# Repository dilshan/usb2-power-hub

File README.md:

4 Port high power USB hub 
=========================

This project is about a high current USB 2.0 hub that is specifically designed to drive USB powered development boards and experimental peripherals.

The core element of this USB hub is the *FE1.1s* USB 2.0 hub controller. The *FE1.1s* is a low cost, 4-port, high-speed USB hub controller you should be able to find on *eBay* or AliExpress.

This USB hub adds the following additional features to those offered by the *FE1.1s*:

 - Switches to on/off and reset individual USB ports.
 - Capability to provide a maximum of 3A of current from each USB port.
 - Power using 9V to 15V DC voltage source.

This USB hub uses a *PIC16F630* MCU and four *LM2596-5.0* switching regulators. 

[You can find everything about how to build and use this project on our wiki.](https://github.com/dilshan/usb2-power-hub/wiki)

Licenses
--------

This is a [certified open hardware project](https://certification.oshwa.org/lk000005.html) and all its design files, firmware source code, documentation, and other resource files are available at this project source repository. The content of this project is distributed under the terms of the following licenses:

 - Hardware License: [CC BY 4.0](https://creativecommons.org/licenses/by/4.0/)
 - Software License: [MIT](https://github.com/dilshan/usb-morse-keyer/blob/master/LICENSE)
 - Documentation License: [CC BY 4.0](https://creativecommons.org/licenses/by/4.0/)

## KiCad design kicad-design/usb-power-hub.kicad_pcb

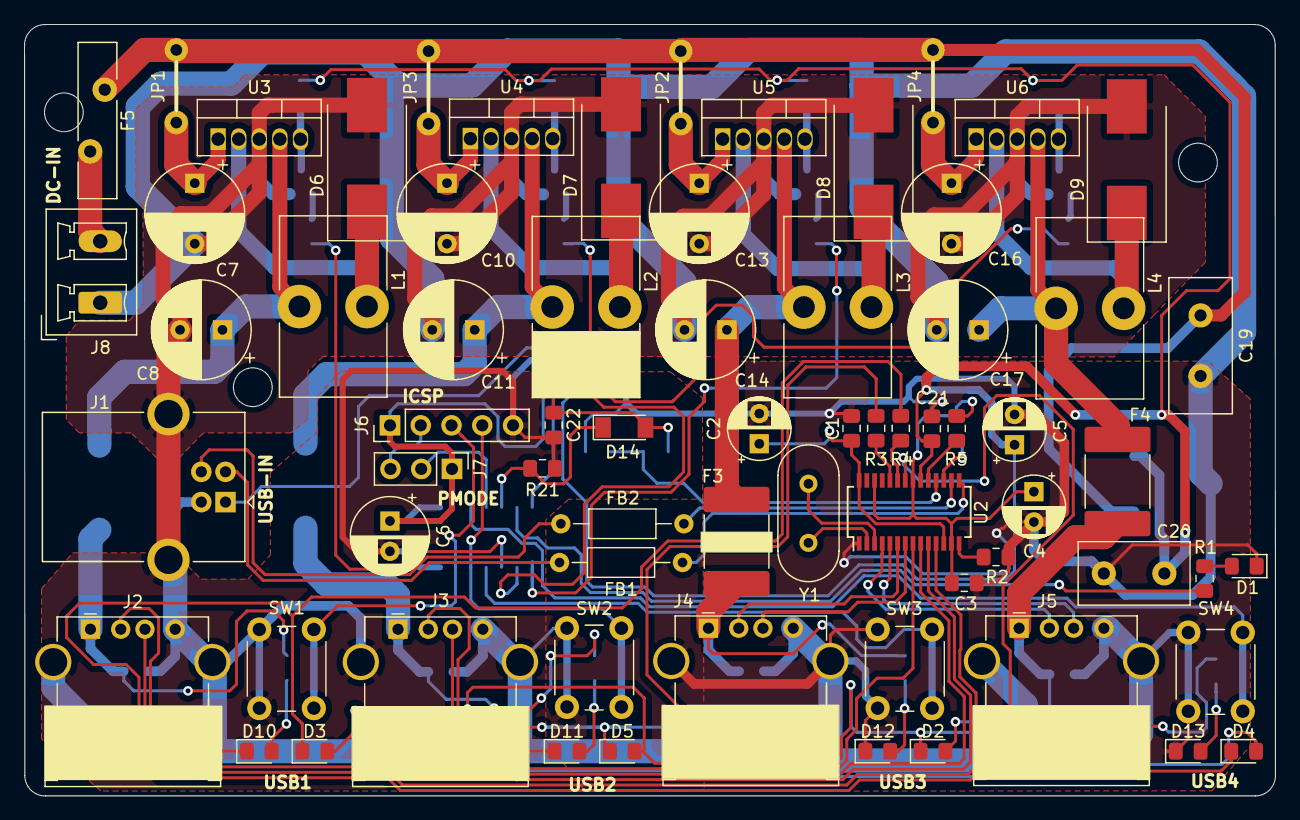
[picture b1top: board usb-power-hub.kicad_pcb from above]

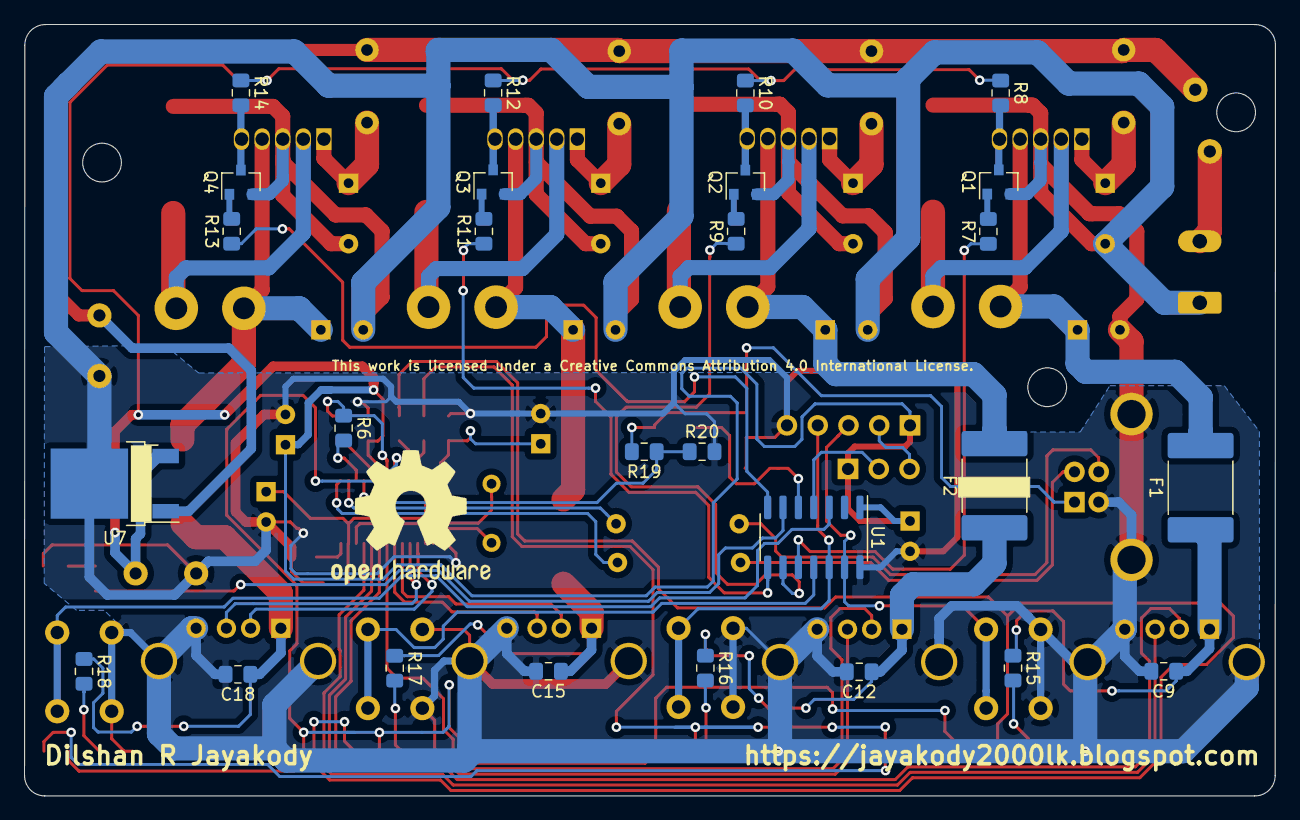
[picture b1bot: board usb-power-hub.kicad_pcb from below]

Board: 2 copper layers, 103.3 x 63.7 mm, 99 parts (27 on the bottom side), 71 nets.

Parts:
 : MountingHole_3.2mm_M3_ISO14580
 #2,  #3: MountingHole_3.2mm_M3_ISO14580
C1, C3, C9, C12, C15, C18, C21, C22: 0.1MFD; C_0805_2012Metric_Pad1.15x1.40mm_HandSolder
C2, C4, C5: 10MFD; CP_Radial_D5.0mm_P2.50mm
C6: 100MFD; CP_Radial_D6.3mm_P2.50mm
C7, C10, C13, C16: 470MFD; CP_Radial_D8.0mm_P5.00mm
C8, C11, C14, C17: 220MFD; CP_Radial_D8.0mm_P3.50mm
C19: 0.33MFD; C_Disc_D11.0mm_W5.0mm_P5.00mm
C20: 0.1MFD; C_Disc_D9.0mm_W5.0mm_P5.00mm
D1: LED-PWR; LED_0805_2012Metric_Pad1.15x1.40mm_HandSolder
D2: LED-P3; LED_0805_2012Metric_Pad1.15x1.40mm_HandSolder
D3: LED-P1; LED_0805_2012Metric_Pad1.15x1.40mm_HandSolder
D4: LED-P4; LED_0805_2012Metric_Pad1.15x1.40mm_HandSolder
D5: LED-P2; LED_0805_2012Metric_Pad1.15x1.40mm_HandSolder
D6, D7, D8, D9: SS34; D_SMC_Handsoldering
D10: LED-PW1; LED_0805_2012Metric_Pad1.15x1.40mm_HandSolder
D11: LED-PW2; LED_0805_2012Metric_Pad1.15x1.40mm_HandSolder
D12: LED-PW3; LED_0805_2012Metric_Pad1.15x1.40mm_HandSolder
D13: LED-PW4; LED_0805_2012Metric_Pad1.15x1.40mm_HandSolder
D14: 1N4148; D_MiniMELF
F1, F2, F3, F4: MF-LSMF300X-2; Fuse_2920_7451Metric_Pad2.10x5.45mm_HandSolder
F5: JK16-800; Fuse_Bourns_MF-RG800
FB1, FB2: BL01RN1A1D2; L_Axial_L5.3mm_D2.2mm_P10.16mm_Horizontal_Vishay_IM-1
J1: USB-HOST; USB_B_OST_USB-B1HSxx_Horizontal
J2, J3, J4, J5: USB_A; USB_A_Stewart_SS-52100-001_Horizontal
J6: ISP; PinHeader_1x05_P2.54mm_Vertical
J7: ISP-ENABLE; PinHeader_1x03_P2.54mm_Vertical
J8: DC-IN; PhoenixContact_MCV_1,5_2-G-5.08_1x02_P5.08mm_Vertical
JP1, JP2, JP3, JP4: Jumper; WireJumper
L1, L2, L3, L4: 33uH; L_Toroid_Vertical_L14.7mm_W8.6mm_P5.58mm_Pulse_KM-1
Q1, Q2, Q3, Q4: J3Y; SOT-23
R1, R3, R4: 2.2K; R_0805_2012Metric_Pad1.15x1.40mm_HandSolder
R2: 2.7K; R_0805_2012Metric_Pad1.15x1.40mm_HandSolder
R5, R6, R20: 100K; R_0805_2012Metric_Pad1.15x1.40mm_HandSolder
R7, R9, R11, R13: 10K; R_0805_2012Metric_Pad1.15x1.40mm_HandSolder
R8, R10, R12, R14: 22K; R_0805_2012Metric_Pad1.15x1.40mm_HandSolder
R15, R16, R17, R18: 5.6K; R_0805_2012Metric_Pad1.15x1.40mm_HandSolder
R19: 51K; R_0805_2012Metric_Pad1.15x1.40mm_HandSolder
R21: 47K; R_0805_2012Metric_Pad1.15x1.40mm_HandSolder
SW1: USB-CON-1; SW_PUSH_6mm
SW2: USB-CON-2; SW_PUSH_6mm
SW3: USB-CON-3; SW_PUSH_6mm
SW4: USB-CON-4; SW_PUSH_6mm
U1: PIC16F630; SOIC-14_3.9x8.7mm_P1.27mm
U2: FE1.1s; SSOP-28_3.9x9.9mm_P0.635mm
U3, U4, U5, U6: LM2596T-5; TO-220-5_Vertical
U7: KA78M05; TO-252-2
Y1: 12.00MHz; Crystal_HC49-U_Vertical

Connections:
+1V8: C1.1, C2.1, U2.12, U2.28
+3V3: C3.1, C4.1, R5.2, R6.1, U2.13, U2.21, U2.26
+5V: C5.1, C6.1, C20.1, C21.1, J6.1, J7.1, R8.1, R10.1, R12.1, R14.1, U1.1, U2.20, U7.3
CN-SENSE: R19.1, R20.1, U2.18
DC-IN1: C7.1, JP1.2, U3.1
DC-IN2: C13.1, JP2.2, U5.1
DC-IN3: C10.1, JP3.2, U4.1
DC-IN4: C16.1, JP4.2, U6.1
DC-IN5: C19.1, F5.1, JP1.1, JP2.1, JP3.1, JP4.1, U7.1
GND: C1.2, C2.2, C3.2, C4.2, C5.2, C6.2, C7.2, C8.2, C9.2, C10.2, C11.2, C12.2, C13.2, C14.2, C15.2, C16.2, C17.2, C18.2, C19.2, C20.2, C21.2, C22.2, D1.1, D6.2, D7.2, D8.2, D9.2, D10.1, D11.1, D12.1, D13.1, J1.4, J1.5, J2.4, J2.5, J3.4, J3.5, J4.4, J4.5, J5.4, J5.5, J6.5, J8.1, Q1.2, Q2.2, Q3.2, Q4.2, R2.2, R20.2, R21.2, SW1.1, SW2.1, SW3.1, SW4.1, U1.14, U2.1, U3.3, U4.3, U5.3, U6.3, U7.2
HOST-DM: FB1.1, U2.15
HOST-DP: FB2.1, U2.16
unnamed: C8.1, F1.2, L1.2, U3.4
unnamed: C11.1, F2.2, L2.2, U4.4
unnamed: C14.1, F3.2, L3.2, U5.4
unnamed: C17.1, F4.2, L4.2, U6.4
unnamed: C22.1, D14.2, J1.1, R19.2
unnamed: D1.2, R1.2
unnamed: D2.1, D3.2, D4.1, D5.2, U2.22
unnamed: D2.2, D3.1, R4.2
unnamed: D4.2, D5.1, R3.2
unnamed: D6.1, L1.1, U3.2
unnamed: D7.1, L2.1, U4.2
unnamed: D8.1, L3.1, U5.2
unnamed: D9.1, L4.1, U6.2
unnamed: D10.2, R15.2
unnamed: D11.2, R16.2
unnamed: D12.2, R17.2
unnamed: D13.2, R18.2
unnamed: F5.2, J8.2
unnamed: FB1.2, J1.2
unnamed: FB2.2, J1.3
unnamed: J6.2, J7.3
unnamed: Q1.1, R7.2
unnamed: Q2.1, R9.2
unnamed: Q3.1, R11.2
unnamed: Q4.1, R13.2
unnamed: R2.1, U2.14
unnamed: R3.1, U2.24
unnamed: R4.1, U2.23
unnamed: R5.1, U2.19
unnamed: R6.2, U2.17
unnamed: U2.2, Y1.2
unnamed: U2.3, Y1.1
PC-SENSE: D14.1, R21.1, U1.5
PWR-IND: R1.1, U1.6
SWITCH1: J6.3, SW1.2, U1.13
SWITCH2: J6.4, SW2.2, U1.12
SWITCH3: SW3.2, U1.11
SWITCH4: SW4.2, U1.3
USB1-5V: C9.1, F1.1, J2.1, R15.1
USB1-DM: J2.2, U2.10
USB1-DP: J2.3, U2.11
USB2-5V: C12.1, F2.1, J3.1, R16.1
USB2-DM: J3.2, U2.8
USB2-DP: J3.3, U2.9
USB3-5V: C15.1, F3.1, J4.1, R17.1
USB3-DM: J4.2, U2.6
USB3-DP: J4.3, U2.7
USB4-5V: C18.1, F4.1, J5.1, R18.1
USB4-DM: J5.2, U2.4
USB4-DP: J5.3, U2.5
USB-PW-CON1: R7.1, U1.10
USB-PW-CON2: R9.1, U1.9
USB-PW-CON3: R11.1, U1.8
USB-PW-CON4: R13.1, U1.7
USB-REG1: Q1.3, R8.2, U3.5
USB-REG2: Q2.3, R10.2, U4.5
USB-REG3: Q3.3, R12.2, U5.5
USB-REG4: Q4.3, R14.2, U6.5
VPP: J7.2, U1.4

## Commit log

2019-10-24 Initial version of design files.
2019-10-24 Add image of the prototype hub.
2019-10-26 Update readme file with documentation details.
2019-10-26 Update readme file with badges.
2019-11-02 Add OSHW certificate image and link.
2019-11-04 Grammar updates to the README
    Simplify and clean up a bit of the language in the README

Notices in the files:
kicad-design/usb-power-hub.kicad_pcb:
This work is licensed under a Creative Commons Attribution 4.0 International License.
